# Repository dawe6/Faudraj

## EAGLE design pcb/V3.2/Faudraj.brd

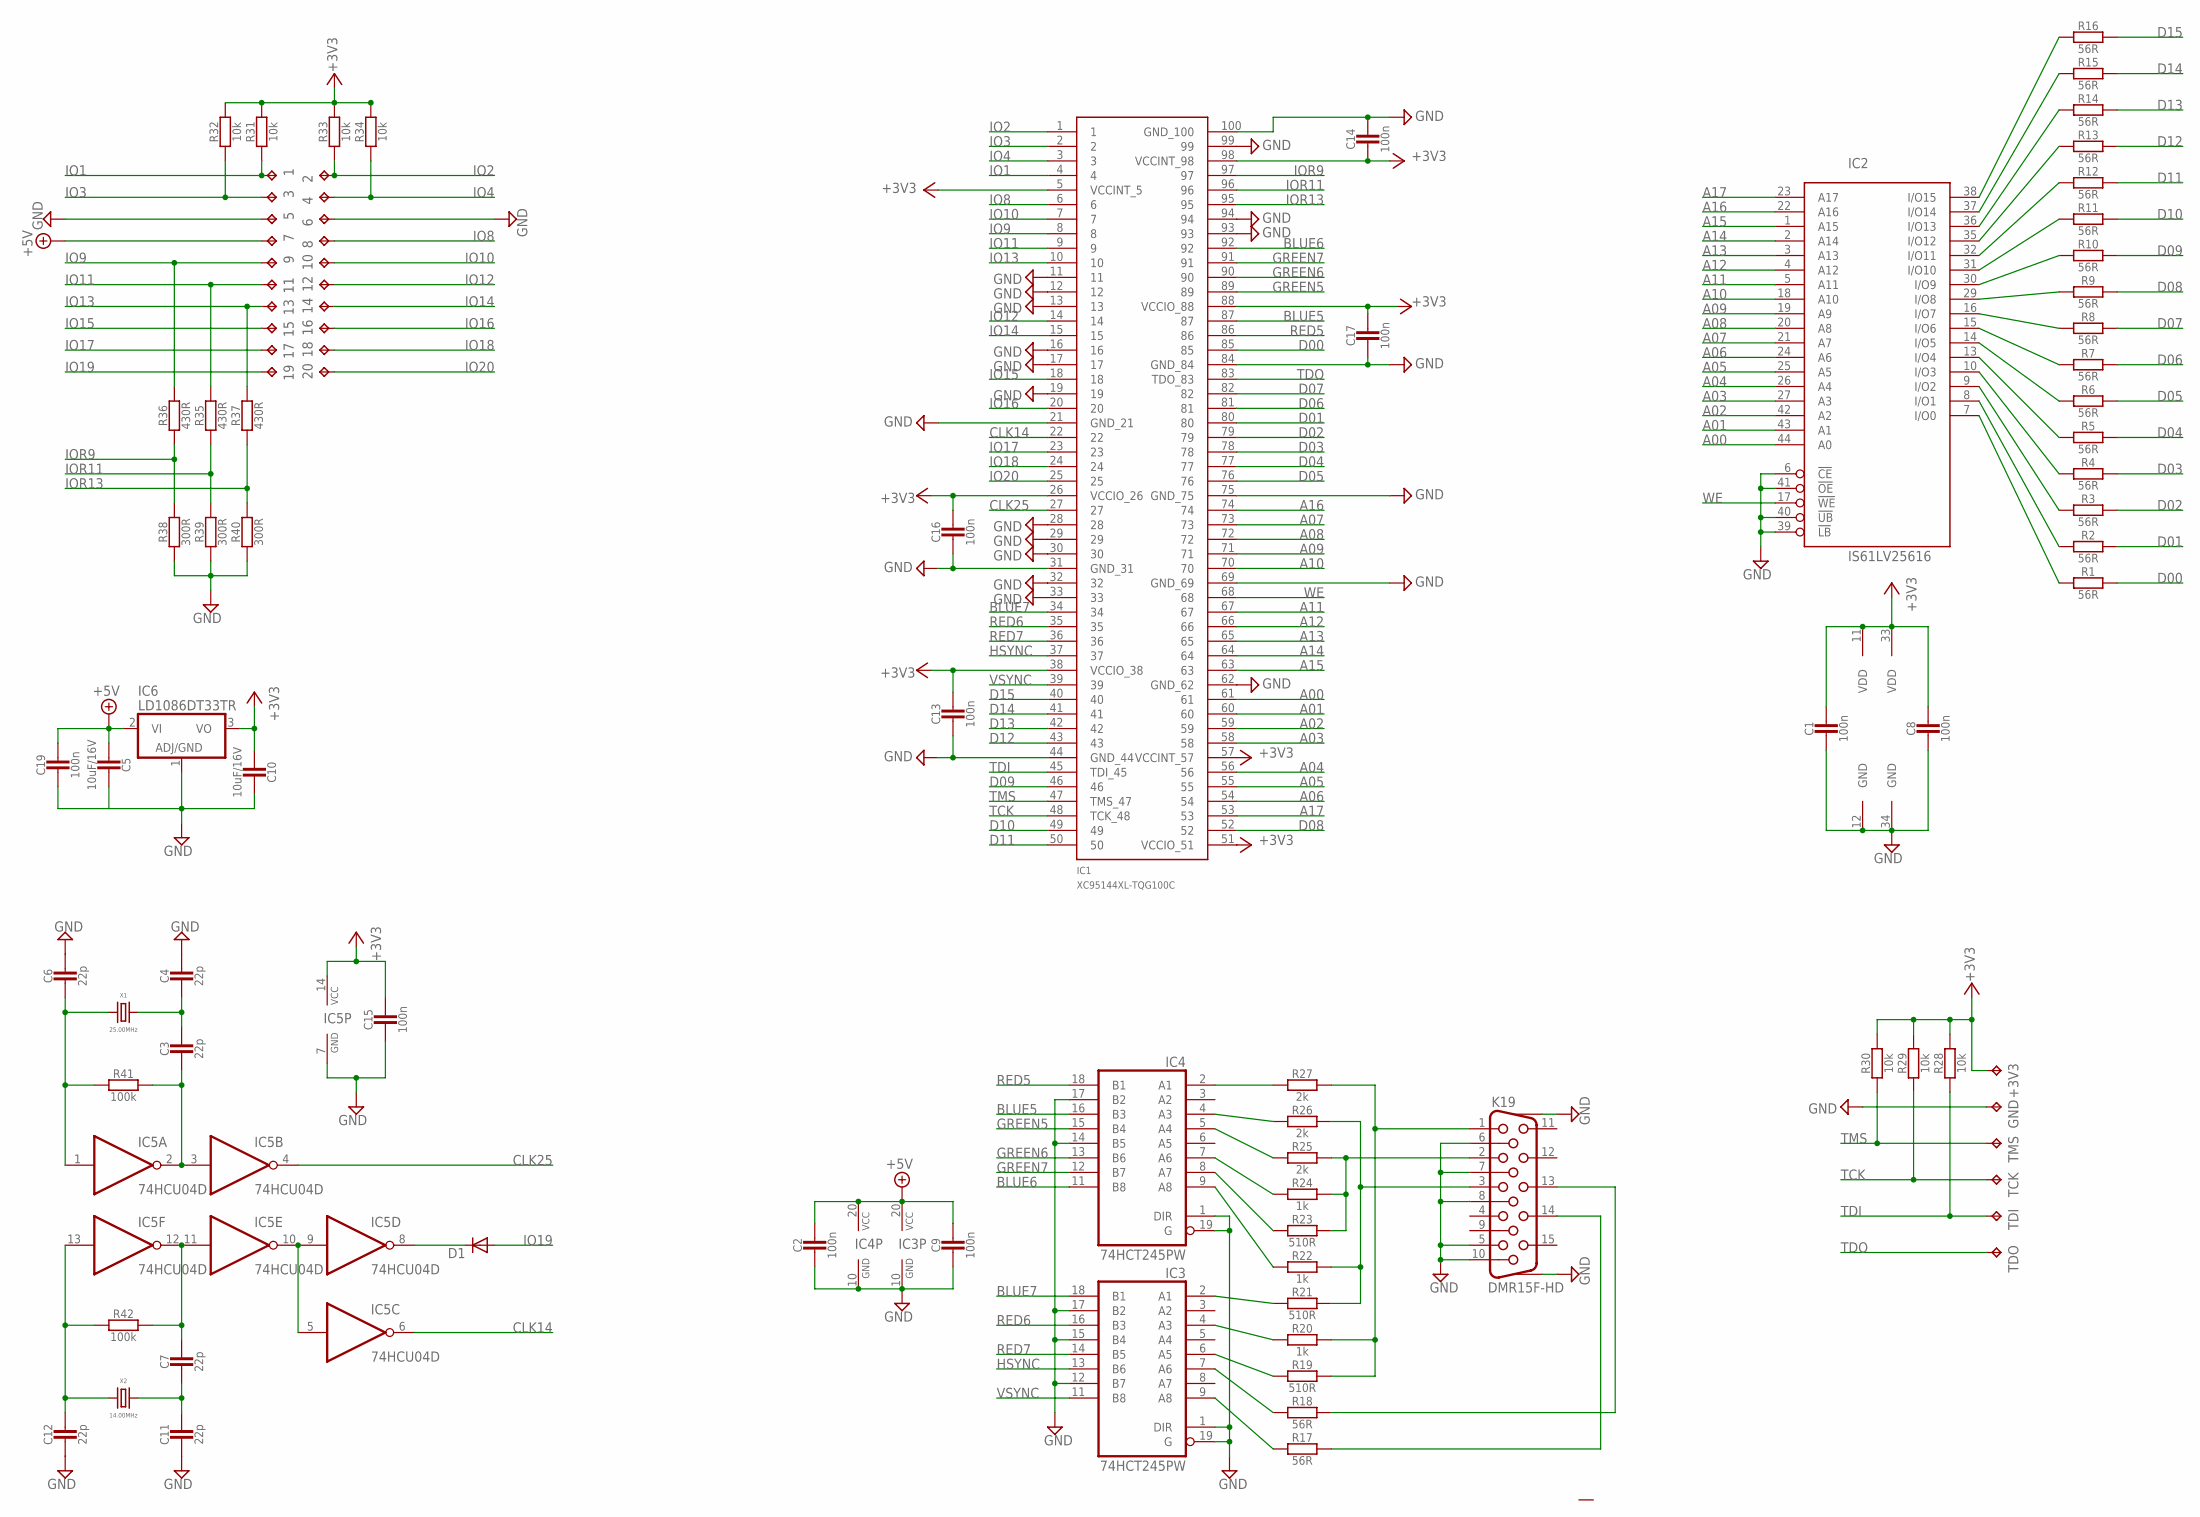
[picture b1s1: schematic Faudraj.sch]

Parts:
1, 2, 3, 4, 5, 6, 7, 8, 9, 10, 11, 12, 13, 14, 15, 16, 17, 18, 19, 20: nic; TP20R
+3V3: nic; TP20R
C1, C2, C8, C9, C13, C14, C15, C16, C17, C19: 100n; SMD0603
C3, C4, C6, C7, C11, C12: 22p; SMD0603
C5, C10: 10uF/16V; SMD1206
D1: DIODE-MINIMELF; MINIMELF
GND: nic; TP20R
IC1: XC95144XL-TQG100C; TQFP100
IC2: IS61LV25616; TSOP-II-44
IC3, IC4: 74HCT245PW; TSSOP20
IC5: 74HCU04D; SO14
IC6: LD1086DT33TR; TO252
K19: DMR15F-HD; HF15G
R1, R2, R3, R4, R5, R6, R7, R8, R9, R10, R11, R12, R13, R14, R15, R16, R17, R18: 56R; SMD0603
R19, R21, R23: 510R; SMD0603
R20, R22, R24: 1k; SMD0603
R25, R26, R27: 2k; SMD0603
R28, R29, R30, R31, R32, R33, R34: 10k; SMD0603
R35, R36, R37: 430R; SMD0603
R38, R39, R40: 300R; SMD0603
R41, R42: 100k; SMD0603
SJ1: nic; OTVOR3.2
TCK: nic; TP20R
TDI: nic; TP20R
TDO: nic; TP20R
TMS: nic; TP20R
X1: 25.00MHz; HC49U-V
X2: 14.00MHz; HC49U-V

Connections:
+3V3: +3V3.TP, C1.1, C8.1, C10.2, C13.1, C14.2, C15.1, C16.1, C17.1, IC1.5 (VCCINT_5), IC1.26 (VCCIO_26), IC1.38 (VCCIO_38), IC1.51 (VCCIO_51), IC1.57 (VCCINT_57), IC1.88 (VCCIO_88), IC1.98 (VCCINT_98), IC2.11 (VDD), IC2.33 (VDD), IC5.14 (VCC), IC6.3 (VO), R28.2, R29.2, R30.2, R31.2, R32.2, R33.2, R34.2
+5V: 7.TP, C2.1, C5.2, C9.1, C19.1, IC3.20 (VCC), IC4.20 (VCC), IC6.2 (VI)
A00: IC1.61, IC2.44 (A0)
A01: IC1.60, IC2.43 (A1)
A02: IC1.59, IC2.42 (A2)
A03: IC1.58, IC2.27 (A3)
A04: IC1.56, IC2.26 (A4)
A05: IC1.55, IC2.25 (A5)
A06: IC1.54, IC2.24 (A6)
A07: IC1.73, IC2.21 (A7)
A08: IC1.72, IC2.20 (A8)
A09: IC1.71, IC2.19 (A9)
A10: IC1.70, IC2.18 (A10)
A11: IC1.67, IC2.5 (A11)
A12: IC1.66, IC2.4 (A12)
A13: IC1.65, IC2.3 (A13)
A14: IC1.64, IC2.2 (A14)
A15: IC1.63, IC2.1 (A15)
A16: IC1.74, IC2.22 (A16)
A17: IC1.53, IC2.23 (A17)
B5: IC4.4 (A3), R26.1
B6: IC4.9 (A8), R22.1
B7: IC3.2 (A1), R21.1
BLUE5: IC1.87, IC4.16 (B3)
BLUE6: IC1.92, IC4.11 (B8)
BLUE7: IC1.34, IC3.18 (B1)
CLK14: IC1.22, IC5.6 (O)
CLK25: IC1.27, IC5.4 (O)
D00: IC1.85, R1.2
D01: IC1.80, R2.2
D02: IC1.79, R3.2
D03: IC1.78, R4.2
D04: IC1.77, R5.2
D05: IC1.76, R6.2
D06: IC1.81, R7.2
D07: IC1.82, R8.2
D08: IC1.52, R9.2
D09: IC1.46, R10.2
D10: IC1.49, R11.2
D11: IC1.50, R12.2
D12: IC1.43, R13.2
D13: IC1.42, R14.2
D14: IC1.41, R15.2
D15: IC1.40, R16.2
G5: IC4.5 (A4), R25.1
G6: IC4.7 (A6), R24.1
G7: IC4.8 (A7), R23.1
GND: 5.TP, 6.TP, C1.2, C2.2, C4.1, C5.1, C6.1, C8.2, C9.2, C10.1, C11.2, C12.2, C13.2, C14.1, C15.2, C16.2, C17.2, C19.2, GND.TP, IC1.11, IC1.12, IC1.13, IC1.16, IC1.17, IC1.19, IC1.21 (GND_21), IC1.28, IC1.29, IC1.30, IC1.31 (GND_31), IC1.32, IC1.33, IC1.44 (GND_44), IC1.62 (GND_62), IC1.69 (GND_69), IC1.75 (GND_75), IC1.84 (GND_84), IC1.93, IC1.94, IC1.99, IC1.100 (GND_100), IC2.6 (!CE), IC2.12 (GND), IC2.34 (GND), IC2.39 (!LB), IC2.40 (!UB), IC2.41 (!OE), IC3.1 (DIR), IC3.10 (GND), IC3.12 (B7), IC3.15 (B4), IC3.17 (B2), IC3.19 (G), IC4.1 (DIR), IC4.10 (GND), IC4.14 (B5), IC4.17 (B2), IC4.19 (G), IC5.7 (GND), IC6.1 (ADJ_GND), K19.5, K19.6, K19.7, K19.8, K19.10, K19.G1, K19.G2, R38.1, R39.1, R40.1
GREEN5: IC1.89, IC4.15 (B4)
GREEN6: IC1.90, IC4.13 (B6)
GREEN7: IC1.91, IC4.12 (B7)
HS: IC3.7 (A6), R18.1
HSYNC: IC1.37, IC3.13 (B6)
IO1: 1.TP, IC1.4, R31.1
IO2: 2.TP, IC1.1, R33.1
IO3: 3.TP, IC1.2, R32.1
IO4: 4.TP, IC1.3, R34.1
IO8: 8.TP, IC1.6
IO9: 9.TP, IC1.8, R36.2
IO10: 10.TP, IC1.7
IO11: 11.TP, IC1.9, R35.2
IO12: 12.TP, IC1.14
IO13: 13.TP, IC1.10, R37.2
IO14: 14.TP, IC1.15
IO15: 15.TP, IC1.18
IO16: 16.TP, IC1.20
IO17: 17.TP, IC1.23
IO18: 18.TP, IC1.24
IO19: 19.TP, D1.A
IO20: 20.TP, IC1.25
IOR9: IC1.97, R36.1, R38.2
IOR11: IC1.96, R35.1, R39.2
IOR13: IC1.95, R37.1, R40.2
unnamed: IC2.7 (I/O0), R1.1
unnamed: IC2.16 (I/O7), R8.1
unnamed: IC2.29 (I/O8), R9.1
unnamed: C6.2, IC5.1 (I), R41.1, X1.2
unnamed: C3.2, IC5.2 (O), IC5.3 (I), R41.2
unnamed: IC2.15 (I/O6), R7.1
unnamed: IC2.14 (I/O5), R6.1
unnamed: IC2.13 (I/O4), R5.1
unnamed: IC2.10 (I/O3), R4.1
unnamed: IC2.9 (I/O2), R3.1
unnamed: IC2.8 (I/O1), R2.1
unnamed: IC2.30 (I/O9), R10.1
unnamed: IC2.31 (I/O10), R11.1
unnamed: IC2.32 (I/O11), R12.1
unnamed: IC2.35 (I/O12), R13.1
unnamed: IC2.36 (I/O13), R14.1
unnamed: IC2.37 (I/O14), R15.1
unnamed: IC2.38 (I/O15), R16.1
unnamed: C3.1, C4.2, X1.1
unnamed: C7.1, IC5.11 (I), IC5.12 (O), R42.2
unnamed: IC5.5 (I), IC5.9 (I), IC5.10 (O)
unnamed: D1.C, IC5.8 (O)
unnamed: C12.1, IC5.13 (I), R42.1, X2.2
unnamed: C7.2, C11.1, X2.1
R5: IC4.2 (A1), R27.1
R6: IC3.4 (A3), R20.1
R7: IC3.6 (A5), R19.1
RED5: IC1.86, IC4.18 (B1)
RED6: IC1.35, IC3.16 (B3)
RED7: IC1.36, IC3.14 (B5)
TCK: IC1.48 (TCK_48), R29.1, TCK.TP
TDI: IC1.45 (TDI_45), R28.1, TDI.TP
TDO: IC1.83 (TDO_83), TDO.TP
TMS: IC1.47 (TMS_47), R30.1, TMS.TP
VGA_BLUE: K19.3, R21.2, R22.2, R26.2
VGA_GREEN: K19.2, R23.2, R24.2, R25.2
VGA_HSYNC: K19.13, R18.2
VGA_RED: K19.1, R19.2, R20.2, R27.2
VGA_VSYNC: K19.14, R17.2
VS: IC3.9 (A8), R17.1
VSYNC: IC1.39, IC3.11 (B8)
WE: IC1.68, IC2.17 (!WE)

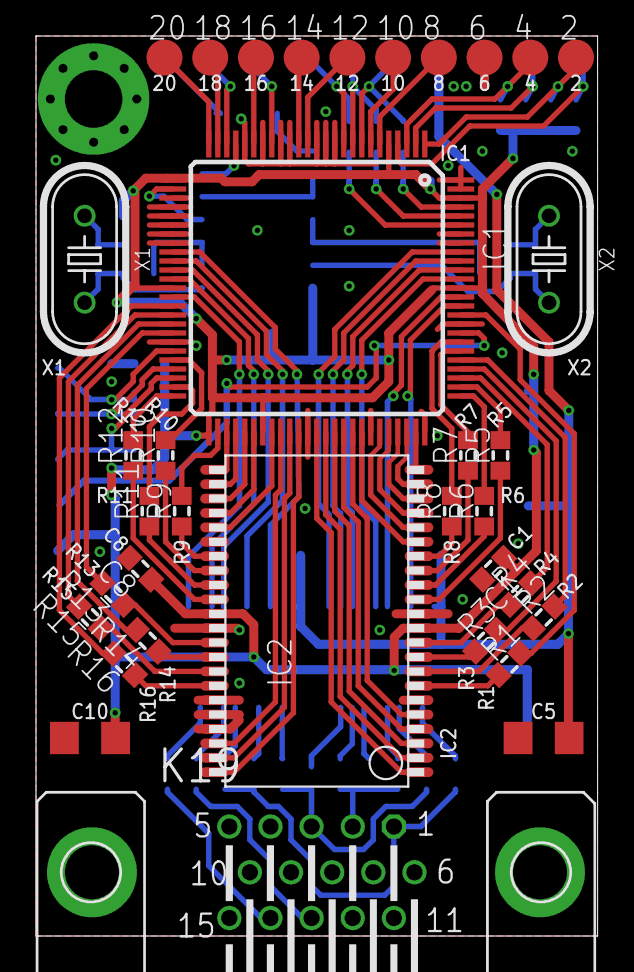
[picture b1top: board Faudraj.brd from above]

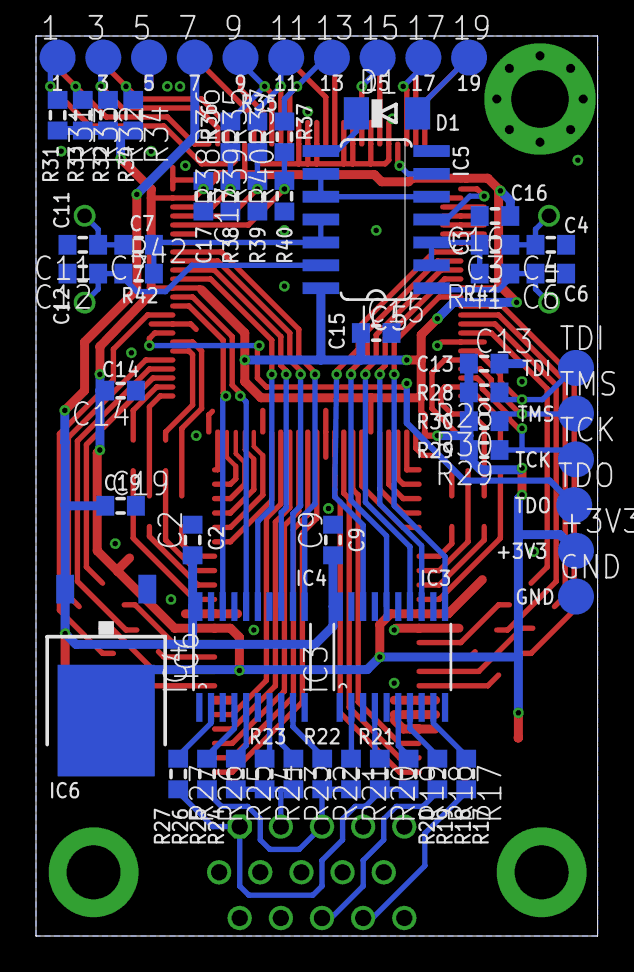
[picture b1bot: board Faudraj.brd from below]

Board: 2 copper layers, 31.2 x 50.0 mm, 97 parts (61 on the bottom side), 115 nets.

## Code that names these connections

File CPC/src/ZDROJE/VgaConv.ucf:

# ============================================================================
# == CPC464, CPC664, CPC6128 Vga konvertor pro hardware Faudraj 3.1	    ==
# ============================================================================
# zapojeni pinu vstupniho konektoru CN2 k Xilinx XC95144XL
NET "SWITCH<0>"		LOC = "P4";			# pin1  - nastavovaci prepinac SW1
NET "SWITCH<1>"		LOC = "P1";			# pin2  - nastavovaci prepinac SW2
NET "SWITCH<2>"		LOC = "P2";			# pin3  - nastavovaci prepinac SW3
NET "SWITCH<3>"		LOC = "P3";			# pin4  - nastavovaci prepinac SW4
							# pin5	- GND
							# pin6	- GND
							# pin7	- Vcc (5V)
							# pin8  - nezapojeno
NET "RGB<0>"		LOC = "P8";			# pin9	- barevna slozka RED signal CPC
NET "HSYNC"		LOC = "P7";			# pin10 - horizontalni synchronizace signal CPC
NET "RGB<2>"		LOC = "P9";			# pin11	- barevna slozka GREEN signal CPC
NET "VSYNC"		LOC = "P14";			# pin12 - vertikalni synchronizace signal CPC
NET "RGB<4>"		LOC = "P10";			# pin13	- barevna slozka BLUE signal CPC
							# pin14 - nezapojeno
							# pin15 - nezapojeno
							# pin16 - nezapojeno
NET "CLK16"		LOC = "P23" | BUFG = CLK;	# pin17 - hodiny 17.734475MHz signal CPC
							# pin18 - nezapojeno
							# pin19	- nezapojeno
							# pin20 - nezapojeno
NET "RGB<1>"		LOC = "P97";	# barevna slozka RED pres odporovy delic
NET "RGB<3>"		LOC = "P96";	# barevna slozka GREEN pres odporovy delic
NET "RGB<5>"		LOC = "P95";	# barevna slozka BLUE pres odporovy delic
# ============================================================================
# zapojeni oscilatoru k Xilinx XC95144XL
NET "CLK25"		LOC = "P27";			# hodiny oscilatoru 74HCU04 (25MHz)
# ============================================================================
# pripojeni VGA pres oddelovac 74x245 a odporove pole
NET "VGARED1"		LOC = "P36";			# cervena slozka vysoka intenzita
NET "VGARED2"		LOC = "P35";			# cervena slozka stredni intenzita
NET "VGARED3"		LOC = "P86";			# cervena slozka nizka intenzita
NET "VGAGRN1"		LOC = "P91";			# zelena slozka vysoka intenzita
NET "VGAGRN2"		LOC = "P90";			# zelena slozka stredni intenzita
NET "VGAGRN3"		LOC = "P89";			# zelena slozka nizka intenzita
NET "VGABLU1"		LOC = "P34";			# modra slozka vysoka intenzita
NET "VGABLU2"		LOC = "P92";			# modra slozka stredni intenzita
NET "VGABLU3"		LOC = "P87";			# modra slozka nizka intenzita
NET "VGAHSYNC"		LOC = "P37";			# horizontalni synchronizace
NET "VGAVSYNC"		LOC = "P39";			# vertikalni synchronizace
# ============================================================================
# zapojeni staticke pameti RAM 256k*16 nebo 64k*16 k Xilinx XC95144XL
NET "RAMWRT"		LOC = "P68";			# povoleni zapisu do ram
NET "RAMADR<0>"		LOC = "P63";			# adresa ram - 256x16 bit0	64x16 bit0
NET "RAMADR<1>"		LOC = "P64";			# adresa ram - 256x16 bit1	64x16 bit1
NET "RAMADR<2>"		LOC = "P65";			# adresa ram - 256x16 bit2	64x16 bit2
NET "RAMADR<3>"		LOC = "P66";			# adresa ram - 256x16 bit3	64x16 bit3
NET "RAMADR<4>"		LOC = "P67";			# adresa ram - 256x16 bit4	64x16 bit4
NET "RAMADR<5>"		LOC = "P70";			# adresa ram - 256x16 bit5	64x16 bit5
NET "RAMADR<6>"		LOC = "P71";			# adresa ram - 256x16 bit6	64x16 bit6
NET "RAMADR<7>"		LOC = "P72";			# adresa ram - 256x16 bit7	64x16 bit7
NET "RAMADR<8>"		LOC = "P73";			# adresa ram - 256x16 bit8	64x16 bit8
NET "RAMADR<9>"		LOC = "P54";			# adresa ram - 256x16 bit11	64x16 bit9
NET "RAMADR<10>"	LOC = "P55";			# adresa ram - 256x16 bit12	64x16 bit10
NET "RAMADR<11>"	LOC = "P56";			# adresa ram - 256x16 bit13	64x16 bit11
NET "RAMADR<12>"	LOC = "P58";			# adresa ram - 256x16 bit14	64x16 bit12
NET "RAMADR<13>"	LOC = "P59";			# adresa ram - 256x16 bit15	64x16 bit13
NET "RAMADR<14>"	LOC = "P60";			# adresa ram - 256x16 bit16	64x16 bit14
NET "RAMADR<15>"	LOC = "P61";			# adresa ram - 256x16 bit17	64x16 bit15
NET "RAMADR<16>"	LOC = "P74";			# adresa ram - 256x16 bit9	n.c.
NET "RAMADR<17>"	LOC = "P53";			# adresa ram - 256x16 bit10	n.c.
NET "RAMDAT<0>"		LOC = "P85";			# ram data - bit0
NET "RAMDAT<1>"		LOC = "P76";			# ram data - bit1
NET "RAMDAT<2>"		LOC = "P77";			# ram data - bit2
NET "RAMDAT<3>"		LOC = "P78";			# ram data - bit3
NET "RAMDAT<4>"		LOC = "P79";			# ram data - bit4
NET "RAMDAT<5>"		LOC = "P80";			# ram data - bit5
NET "RAMDAT<6>"		LOC = "P81";			# ram data - bit6
NET "RAMDAT<7>"		LOC = "P82";			# ram data - bit7
NET "RAMDAT<8>"		LOC = "P52";			# ram data - bit 8
NET "RAMDAT<9>"		LOC = "P46";			# ram data - bit 9
NET "RAMDAT<10>"	LOC = "P49";			# ram data - bit 10
NET "RAMDAT<11>"	LOC = "P50";			# ram data - bit 11
NET "RAMDAT<12>"	LOC = "P43";			# ram data - bit 12
NET "RAMDAT<13>"	LOC = "P42";			# ram data - bit 13
NET "RAMDAT<14>"	LOC = "P41";			# ram data - bit 14
NET "RAMDAT<15>"	LOC = "P40";			# ram data - bit 15

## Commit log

2024-11-27 Create LICENCE
2024-11-27 Update LICENCE
2024-11-27 Create LICENSE
